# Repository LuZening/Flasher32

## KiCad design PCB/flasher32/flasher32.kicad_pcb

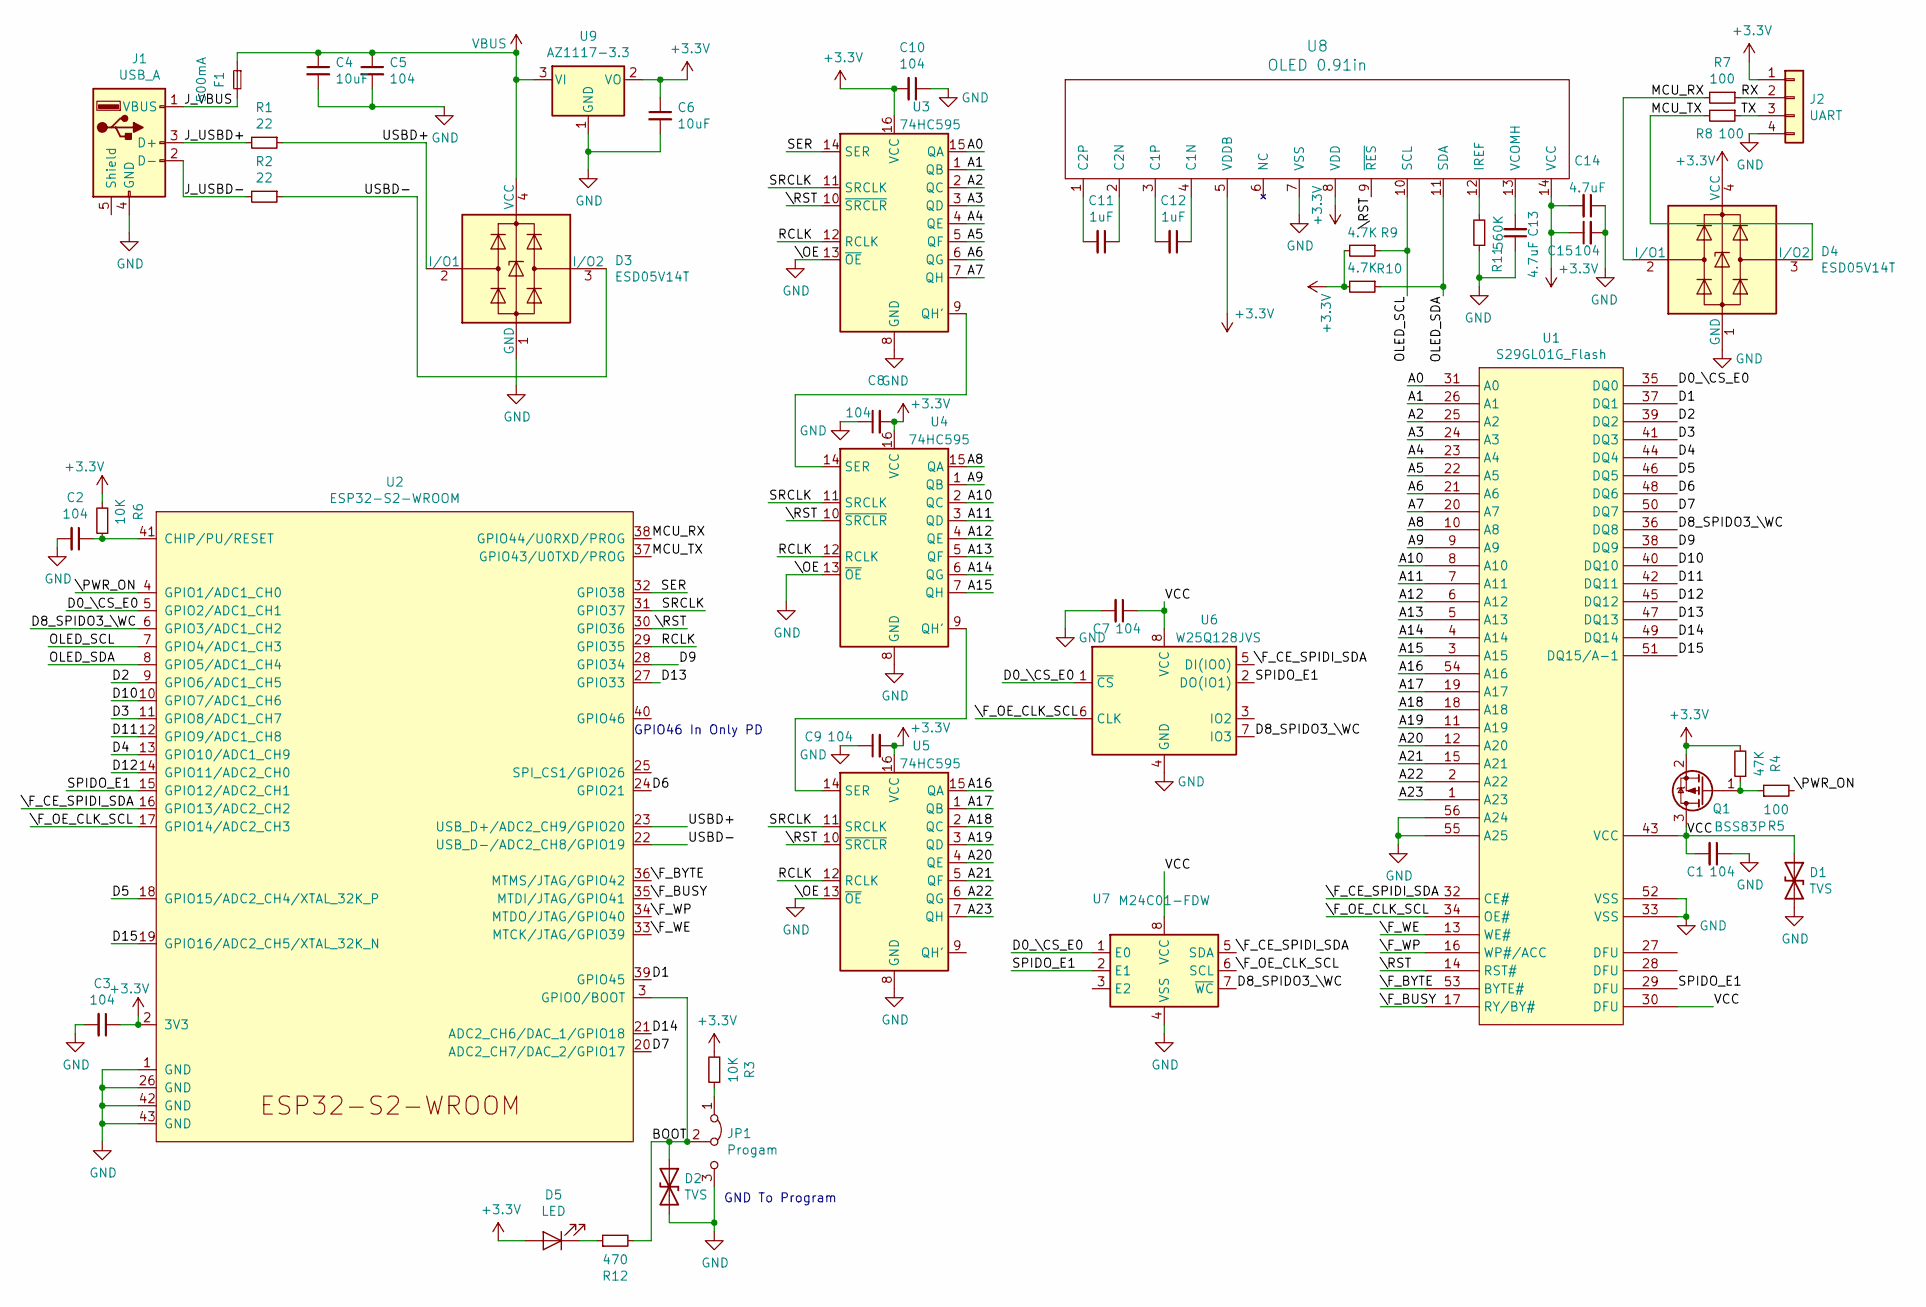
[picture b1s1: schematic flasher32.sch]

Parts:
C1, C2, C3, C5, C7, C8, C9, C10, C15: 104; 0805_C
C4, C6: 10uF; 0805_C
C11, C12: 1uF; 0805_C
C13, C14: 4.7uF; 0805_C
D1, D2: TVS; SOD-123
D3, D4: ESD05V14T; SOT-143
D5: LED; 0805_LED_S1
F1: 500mA; 0805_L
J1: USB_A; USB_Male_A_UP2-AH-1-TH
J2: UART; PinSocket_1x04_P2.54mm_Vertical
JP1: Progam; PinSocket_1x03_P2.54mm_Vertical
Q1: BSS83P; SOT-23
R1, R2: 22; 0805_R
R3, R6: 10K; 0805_R
R4: 47K; 0805_R
R5, R7, R8: 100; 0805_R
R9, R10: 4.7K; 0805_R
R11: 560K; 0805_R
R12: 470; 0805_R
U1: S29GL01G_Flash; TSOP56_Flasher_Socket
U2: ESP32-S2-WROOM
U3, U4, U5: 74HC595; SOP-16_150MIL
U6: W25Q128JVS; SOIC-8_5.23x5.23mm_P1.27mm
U7: M24C01-FDW; TSSOP-8_4.4x3mm_P0.65mm
U8: OLED 0.91in; SSD1306_OLED-0.91-128x32_Fold
U9: AZ1117-3.3; SOT-223

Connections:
+3V3: C3.1, C6.1, C8.2, C9.2, C10.2, C14.2, C15.1, D4.4 (VCC), D5.A, J2.1, Q1.2 (S), R3.2, R4.2, R6.2, R9.2, R10.2, U2.2 (3V3), U3.16 (VCC), U4.16 (VCC), U5.16 (VCC), U8.5 (VDDB), U8.8 (VDD), U8.14 (VCC), U9.2 (VO); also elsewhere on the board
/A0: U1.31 (A0), U3.15 (QA)
/A1: U1.26 (A1), U3.1 (QB)
/A2: U1.25 (A2), U3.2 (QC)
/A3: U1.24 (A3), U3.3 (QD)
/A4: U1.23 (A4), U3.4 (QE)
/A5: U1.22 (A5), U3.5 (QF)
/A6: U1.21 (A6), U3.6 (QG)
/A7: U1.20 (A7), U3.7 (QH)
/A8: U1.10 (A8), U4.15 (QA)
/A9: U1.9 (A9), U4.1 (QB)
/A10: U1.8 (A10), U4.2 (QC)
/A11: U1.7 (A11), U4.3 (QD)
/A12: U1.6 (A12), U4.4 (QE)
/A13: U1.5 (A13), U4.5 (QF)
/A14: U1.4 (A14), U4.6 (QG)
/A15: U1.3 (A15), U4.7 (QH)
/A16: U1.54 (A16), U5.15 (QA)
/A17: U1.19 (A17), U5.1 (QB)
/A18: U1.18 (A18), U5.2 (QC)
/A19: U1.11 (A19), U5.3 (QD)
/A20: U1.12 (A20), U5.4 (QE)
/A21: U1.15 (A21), U5.5 (QF)
/A22: U1.2 (A22), U5.6 (QG)
/A23: U1.1 (A23), U5.7 (QH)
/BOOT: D2.1 (A1), JP1.2 (C), R12.2, U2.3 (GPIO0/BOOT)
/D0_\CS_E0: U1.35 (DQ0), U2.5 (GPIO2/ADC1_CH1), U6.1 (~CS), U7.1 (E0)
/D1: U1.37 (DQ1), U2.39 (GPIO45)
/D2: U1.39 (DQ2), U2.9 (GPIO6/ADC1_CH5)
/D3: U1.41 (DQ3), U2.11 (GPIO8/ADC1_CH7)
/D4: U1.44 (DQ4), U2.13 (GPIO10/ADC1_CH9)
/D5: U1.46 (DQ5), U2.18 (GPIO15/ADC2_CH4/XTAL_32K_P)
/D6: U1.48 (DQ6), U2.24 (GPIO21)
/D7: U1.50 (DQ7), U2.20 (ADC2_CH7/DAC_2/GPIO17)
/D8_SPIDO3_\WC: U1.36 (DQ8), U2.6 (GPIO3/ADC1_CH2), U6.7 (IO3), U7.7 (~WC)
/D9: U1.38 (DQ9), U2.28 (GPIO34)
/D10: U1.40 (DQ10), U2.10 (GPIO7/ADC1_CH6)
/D11: U1.42 (DQ11), U2.12 (GPIO9/ADC1_CH8)
/D12: U1.45 (DQ12), U2.14 (GPIO11/ADC2_CH0)
/D13: U1.47 (DQ13), U2.27 (GPIO33)
/D14: U1.49 (DQ14), U2.21 (ADC2_CH6/DAC_1/GPIO18)
/D15: U1.51 (DQ15/A-1), U2.19 (GPIO16/ADC2_CH5/XTAL_32K_N)
/J_USBD+: J1.3 (D+), R1.2
/J_USBD-: J1.2 (D-), R2.2
/J_VBUS: F1.2, J1.1 (VBUS)
/MCU_RX: D4.2 (I/O1), R7.2, U2.38 (GPIO44/U0RXD/PROG)
/MCU_TX: D4.3 (I/O2), R8.2, U2.37 (GPIO43/U0TXD/PROG)
/OLED_SCL: R9.1, U2.7 (GPIO4/ADC1_CH3), U8.10 (SCL)
/OLED_SDA: R10.1, U2.8 (GPIO5/ADC1_CH4), U8.11 (SDA)
/RCLK: U2.29 (GPIO35), U3.12 (RCLK), U4.12 (RCLK), U5.12 (RCLK)
/RX: J2.2, R7.1; also elsewhere on the board
/SER: U2.32 (GPIO38), U3.14 (SER)
/SPIDO_E1: U1.29 (DFU), U2.15 (GPIO12/ADC2_CH1), U6.2 (DO(IO1)), U7.2 (E1)
/SRCLK: U2.31 (GPIO37), U3.11 (SRCLK), U4.11 (SRCLK), U5.11 (SRCLK)
/TX: J2.3, R8.1; also elsewhere on the board
/USBD+: D3.2 (I/O1), R1.1, U2.23 (USB_D+/ADC2_CH9/GPIO20)
/USBD-: D3.3 (I/O2), R2.1, U2.22 (USB_D-/ADC2_CH8/GPIO19)
/VCC: C1.2, C7.1, D1.1 (A1), Q1.3 (D), U1.30 (DFU), U1.43 (VCC), U6.8 (VCC), U7.8 (VCC)
/\F_BUSY: U1.17 (RY/BY#), U2.35 (MTDI/JTAG/GPIO41)
/\F_BYTE: U1.53 (BYTE#), U2.36 (MTMS/JTAG/GPIO42)
/\F_CE_SPIDI_SDA: U1.32 (CE#), U2.16 (GPIO13/ADC2_CH2), U6.5 (DI(IO0)), U7.5 (SDA)
/\F_OE_CLK_SCL: U1.34 (OE#), U2.17 (GPIO14/ADC2_CH3), U6.6 (CLK), U7.6 (SCL)
/\F_WE: U1.13 (WE#), U2.33 (MTCK/JTAG/GPIO39)
/\F_WP: U1.16 (WP#/ACC), U2.34 (MTDO/JTAG/GPIO40)
/\PWR_ON: R5.2, U2.4 (GPIO1/ADC1_CH0)
/\RST: U1.14 (RST#), U2.30 (GPIO36), U3.10 (~SRCLR), U4.10 (~SRCLR), U5.10 (~SRCLR), U8.9 (~RES)
GND: C1.1, C2.2, C3.2, C4.2, C5.2, C6.2, C7.2, C8.1, C9.1, C10.1, C13.1, C14.1, C15.2, D1.2 (A2), D2.2 (A2), D3.1 (GND), D4.1 (GND), J1.4 (GND), J2.4, JP1.3 (B), R11.1, U1.33 (VSS), U1.52 (VSS), U1.55 (A25), U1.56 (A24), U2.1 (GND), U2.26 (GND), U2.42 (GND), U2.43 (GND), U3.8 (GND), U3.13 (~OE), U4.8 (GND), U4.13 (~OE), U5.8 (GND), U5.13 (~OE), U6.4 (GND), U7.4 (VSS), U8.7 (VSS), U9.1 (GND); also elsewhere on the board
unnamed: C2.1, R6.1, U2.41 (CHIP/PU/RESET)
unnamed: C11.1, U8.2 (C2N)
unnamed: C11.2, U8.1 (C2P)
unnamed: C12.1, U8.4 (C1N)
unnamed: C12.2, U8.3 (C1P)
unnamed: C13.2, U8.13 (VCOMH)
unnamed: D5.K, R12.1
unnamed: JP1.1 (A), R3.1
unnamed: Q1.1 (G), R4.1, R5.1
unnamed: R11.2, U8.12 (IREF)
unnamed: U3.9 (QH'), U4.14 (SER)
unnamed: U4.9 (QH'), U5.14 (SER)
VBUS: C4.1, C5.1, D3.4 (VCC), F1.1, U9.3 (VI)

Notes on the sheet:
GND To Program
GPIO46 In Only PD

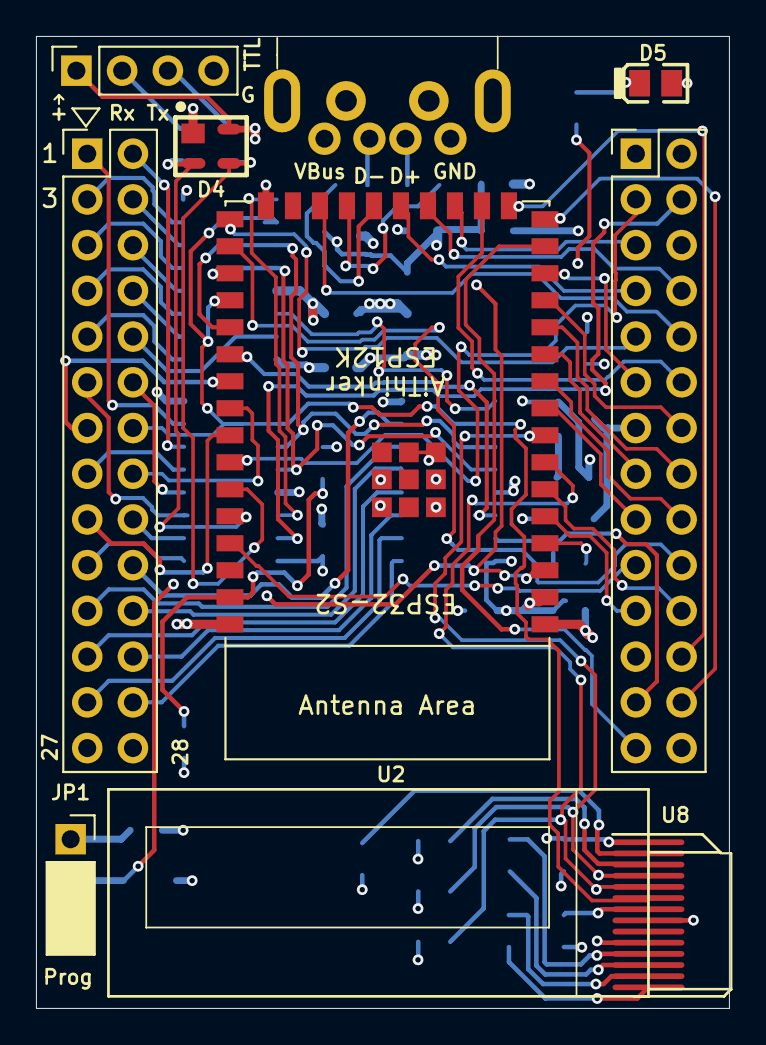
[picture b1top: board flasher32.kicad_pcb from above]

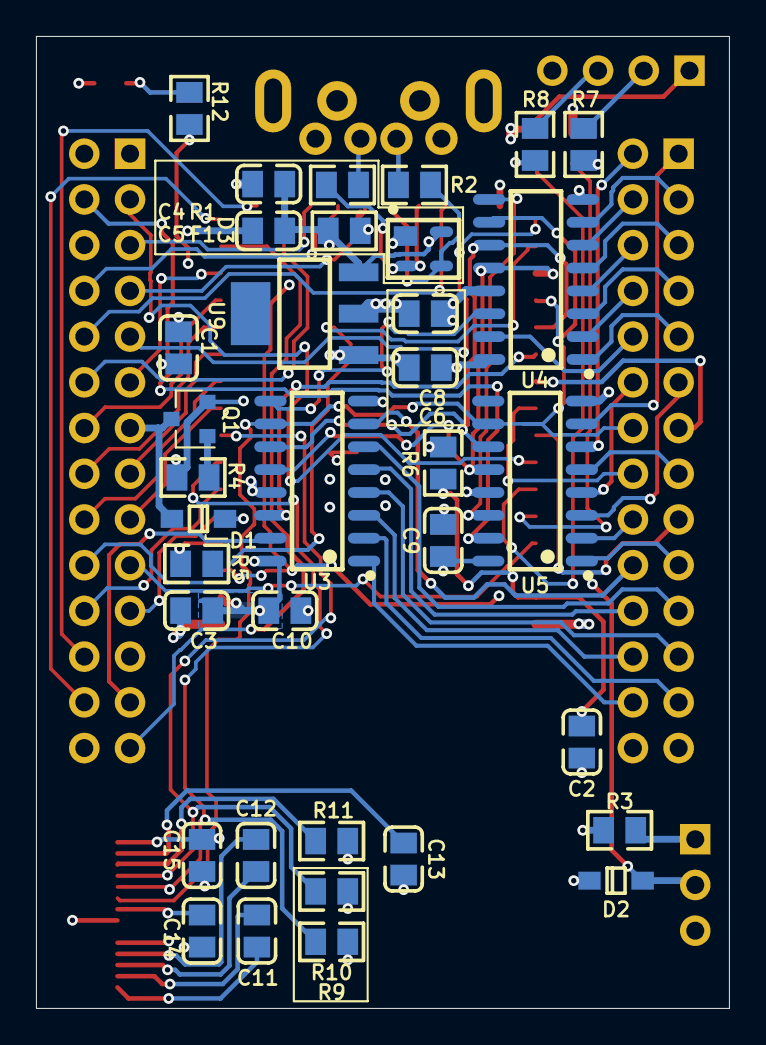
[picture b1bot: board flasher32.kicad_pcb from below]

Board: 4 copper layers, 38.5 x 54.0 mm, 43 parts (35 on the bottom side), 80 nets.

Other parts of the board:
TTL: UART; PinSocket_1x04_P2.54mm_Vertical

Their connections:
+3V3: TTL.1; also elsewhere on the board
/RX: TTL.2; also elsewhere on the board
/TX: TTL.3; also elsewhere on the board
GND: TTL.4; also elsewhere on the board
